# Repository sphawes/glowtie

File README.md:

## Connecting to your Glowtie

### Android

1. Turn on your Glowtie. There’s a power switch next to the micro usb jack. You should see a gold burst animation; this means the Wifi network has started.
1. On your Android phone, turn off your mobile data. This is so that your phone doesn’t try to reach the actual internet instead of the Glowtie.
1. Open your Wifi settings and look for a network named in the format “AdjectiveClothing”. For example, it could be “FancyPants” or “CoolCoat”. This is the Serial Name of your Glowtie. Connect to the network.
1. You may get a notification that the network you connected to does not have internet access, no worries! Just choose the option to stay connected if you are provided with one.
1. Now open a new tab in Google Chrome and enter the following in the address field: http://192.168.4.1
1. You should see the Glowtie control page! In your Chrome settings, choose to “Add to Home screen” to make it easier to get to in the future.

### iPhone

1. Turn on your Glowtie. You should see a gold burst animation; this means the Wifi network has started.
1. On your iPhone, navigate to Settings -> Cellular and toggle Cellular Data off. This is so that your phone doesn’t try to reach the actual internet instead of the Glowtie.
1. Open your Wifi settings and look for a network named in the format “AdjectiveClothing”. For example, it could be “FancyPants” or “CoolCoat”. This is the Serial Name of your Glowtie. Connect to the network.
1. You may get a notification that the network you connected to does not have internet access, no worries! Just choose the option to stay connected if you are provided with one.
1. Now open a new tab in Safari or Google Chrome and enter the following in the address field: http://192.168.4.1
1. You should see the Glowtie control page! In your Chrome settings, choose to “Add to Home screen” to make it easier to get to in the future. In Safari, tap the share button and select “Add to Home Screen” to do the same.

## Usage

When you load the Glowtie website, you’ll see three sliders. These represent the red, green, and blue values of the lights. When you adjust them, the title background will adjust to show you what color you’re set to.

Once you pick a color, there’s a few options for animations. Tap the button next to the animation you want, then hit the “UPDATE” button. Your Glowtie will change to whatever you selected!

The Glowtie has a built-in memory function, so once you choose a color and animation it’ll remember your choice after you turn it off. This way, you don’t need to connect to it every time you turn it on if you have it set to your favorite pattern.

## Charging

When the Glowtie has low battery, the center LED will turn red. Use a Micro USB cable to recharge your Glowtie. Make sure your Glowtie is turned off, then plug the Micro USB cable into the port next to the power switch. When you plug the other end into a USB port for power, you should see the **top** light on your Glowtie illuminate. When it’s done charging, the **bottom** light will illuminate.

## Cover

Your Glowtie optionally has a diffusion cover. The cover is held on with a friction fit. Laser cut or print `diffusion.dxf` in a white or clear material, 1/16" thick. Print `bumper.stl` in a color of your choice, and super glue the diffusion inside the bumper. The bumper can now be friction fit onto the Glowtie.

## HACK!

The Glowtie is totally open-source. All PCB design files, firmware, and physical parts are hosted on the Github page. There’s a dedicated programming header on the left side so you can add your own animations, or make it do anything you want! Just solder on a few pins and reprogram the ESP8266 over UART.

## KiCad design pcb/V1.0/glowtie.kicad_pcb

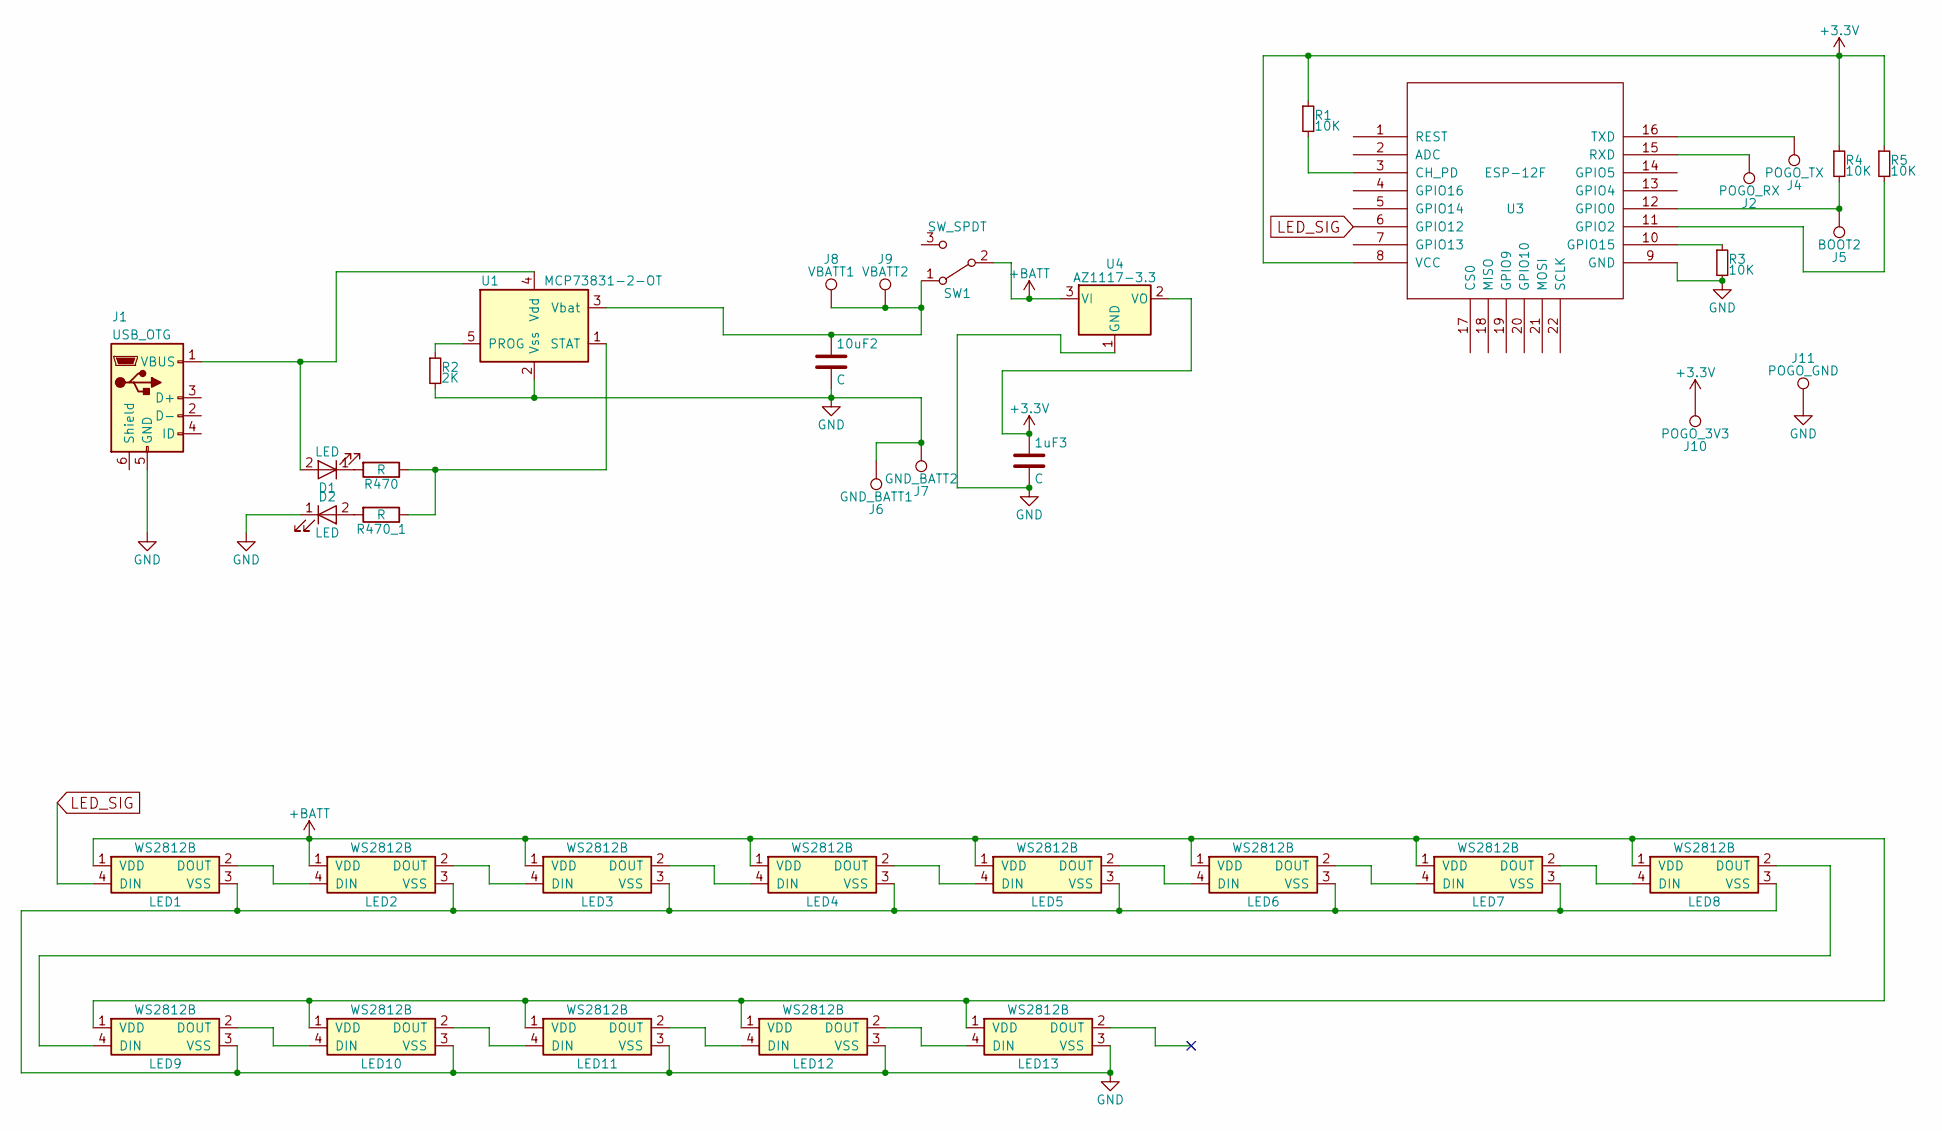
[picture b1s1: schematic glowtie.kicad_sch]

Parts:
1uF3, 10uF2: C; C_0805
D1, D2: LED; LED_0805
J1: USB_OTG; USB_Micro-B
J2: POGO_RX; TestPoint_Pad_D1.5mm
J4: POGO_TX; TestPoint_Pad_D1.5mm
J5: BOOT2; TestPoint_Pad_D1.5mm
J6: GND_BATT1; Measurement_Point_Square-SMD-Pad_Big
J7: GND_BATT2; Measurement_Point_Square-SMD-Pad_Big
J8: VBATT1; Measurement_Point_Round-SMD-Pad_Big
J9: VBATT2; Measurement_Point_Round-SMD-Pad_Big
J10: POGO_3V3; TestPoint_Pad_D1.5mm
J11: POGO_GND; TestPoint_Pad_D1.5mm
LED1, LED2, LED3, LED4, LED5, LED6, LED7, LED8, LED9, LED10, LED11, LED12, LED13: WS2812B; LED_WS2812B-PLCC4
R1, R3, R4, R5: 10K; R_0805
R2: 2K; R_0805
R470, R470_1: R; R_0805
SW1: SW_SPDT; SW_SPDT_PCM12
U1: MCP73831-2-OT; SOT-23-5
U3: ESP-12F; ESP-12E_SMD
U4: AZ1117-3.3; SOT-223-3_TabPin2

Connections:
+3V3: 1uF3.1, J10.1, R1.1, R4.1, R5.1, U3.8 (VCC), U4.2 (VO)
+BATT: LED1.1 (VDD), LED2.1 (VDD), LED3.1 (VDD), LED4.1 (VDD), LED5.1 (VDD), LED6.1 (VDD), LED7.1 (VDD), LED8.1 (VDD), LED9.1 (VDD), LED10.1 (VDD), LED11.1 (VDD), LED12.1 (VDD), LED13.1 (VDD), SW1.2 (B), U4.3 (VI)
GND: 1uF3.2, 10uF2.2, D2.1 (K), J1.5 (GND), J6.1, J7.1, J11.1, LED1.3 (VSS), LED2.3 (VSS), LED3.3 (VSS), LED4.3 (VSS), LED5.3 (VSS), LED6.3 (VSS), LED7.3 (VSS), LED8.3 (VSS), LED9.3 (VSS), LED10.3 (VSS), LED11.3 (VSS), LED12.3 (VSS), LED13.3 (VSS), R2.2, R3.2, U1.2 (Vss), U3.9 (GND), U4.1 (GND)
LED_SIG: LED1.4 (DIN), U3.6 (GPIO12)
unnamed: D1.2 (A), J1.1 (VBUS), U1.4 (Vdd)
unnamed: D1.1 (K), R470.2
unnamed: D2.2 (A), R470_1.2
unnamed: LED1.2 (DOUT), LED2.4 (DIN)
unnamed: LED2.2 (DOUT), LED3.4 (DIN)
unnamed: LED3.2 (DOUT), LED4.4 (DIN)
unnamed: LED4.2 (DOUT), LED5.4 (DIN)
unnamed: LED5.2 (DOUT), LED6.4 (DIN)
unnamed: LED6.2 (DOUT), LED7.4 (DIN)
unnamed: LED7.2 (DOUT), LED8.4 (DIN)
unnamed: LED8.2 (DOUT), LED9.4 (DIN)
unnamed: LED9.2 (DOUT), LED10.4 (DIN)
unnamed: LED10.2 (DOUT), LED11.4 (DIN)
unnamed: LED11.2 (DOUT), LED12.4 (DIN)
unnamed: LED12.2 (DOUT), LED13.4 (DIN)
unnamed: 10uF2.1, J8.1, J9.1, SW1.1 (A), U1.3 (Vbat)
unnamed: R2.1, U1.5 (PROG)
unnamed: R470.1, R470_1.1, U1.1 (STAT)
unnamed: R1.2, U3.3 (CH_PD)
unnamed: J5.1, R4.2, U3.12 (GPIO0)
unnamed: R5.2, U3.11 (GPIO2)
unnamed: R3.1, U3.10 (GPIO15)
unnamed: J2.1, U3.15 (RXD)
unnamed: J4.1, U3.16 (TXD)

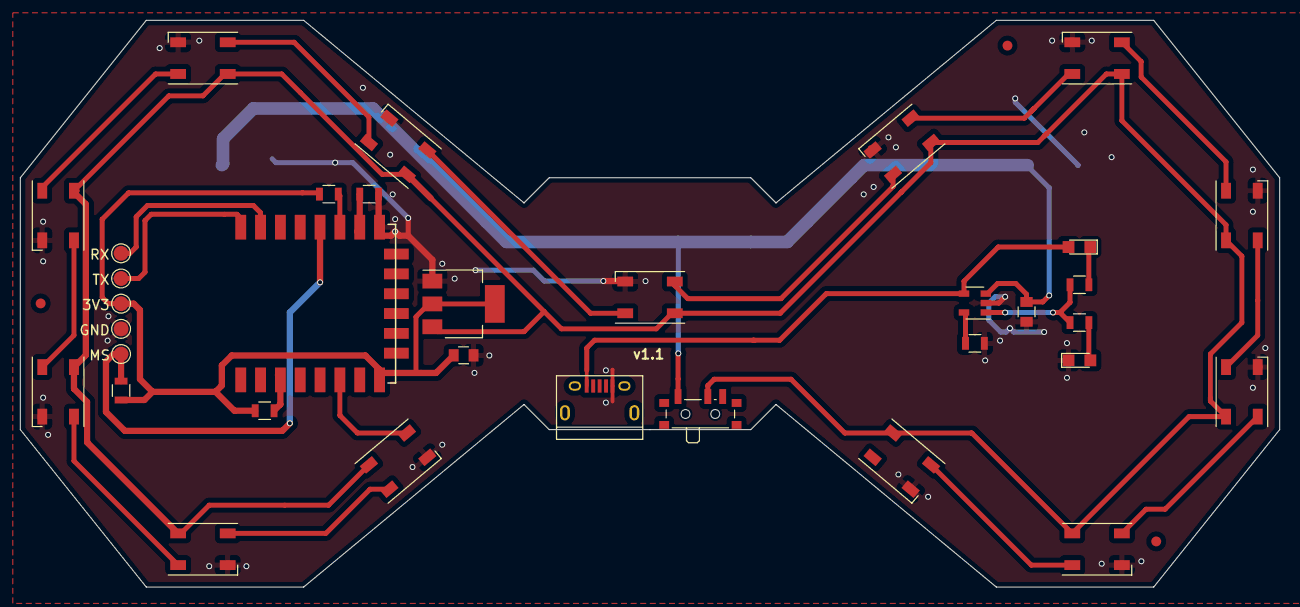
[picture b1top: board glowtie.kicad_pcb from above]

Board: 2 copper layers, 127.0 x 57.1 mm, 38 parts (0 on the bottom side), 28 nets.

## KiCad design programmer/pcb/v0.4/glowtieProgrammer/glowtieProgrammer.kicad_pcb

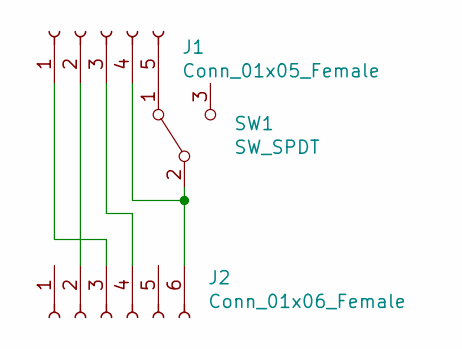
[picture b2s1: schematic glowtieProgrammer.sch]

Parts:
J1: Conn_01x05_Female; Pin_Header_Straight_1x05_Pitch2.54mm
J2: Conn_01x06_Female; Pin_Header_Straight_1x06_Pitch2.54mm
SW1: SW_SPDT; SW_SPDT_PCM12

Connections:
unnamed: J1.1, J2.3
unnamed: J1.2, J2.2
unnamed: J1.3, J2.4
unnamed: J1.4, J2.6, SW1.2 (B)
unnamed: J1.5, SW1.1 (A)

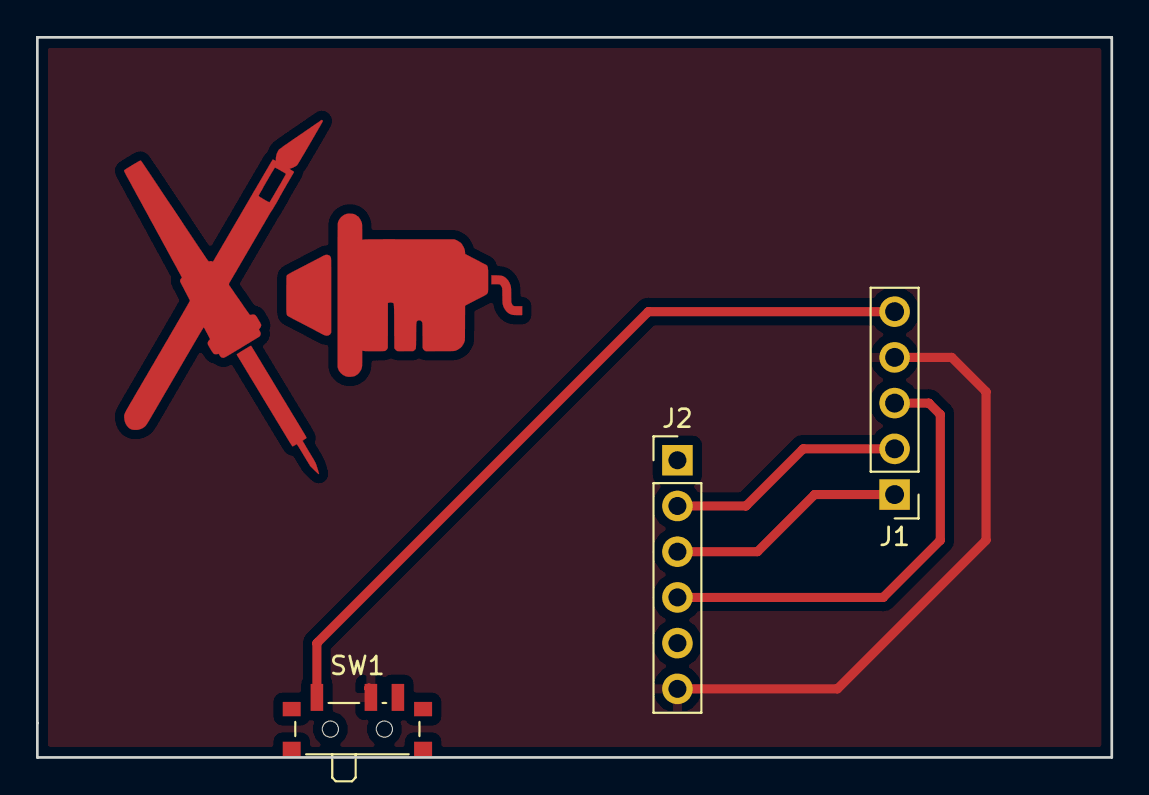
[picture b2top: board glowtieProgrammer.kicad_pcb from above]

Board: 2 copper layers, 59.7 x 40.0 mm, 3 parts (0 on the bottom side), 5 nets.

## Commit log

2019-02-02 adding directory for v0.4 firmware and boot test firmware
2019-02-02 made boot burst gold, firmware flash default mode 0, and added eeprom for color and mode selection between boots
2019-02-03 readme formatting
2019-02-03 adding line art image
2019-02-03 added image to readme
2019-02-17 added programmer cad, updated glowtie cad, cleaned up directory structure
2019-02-17 added images, updated readme
2019-05-19 second to last firmware push
2019-07-28 updated firmware and cad for v1.0
2020-02-11 Set theme jekyll-theme-slate
2023-07-29 updating pcb to v1.1 with better grounding, more widely used LDO pinout
2023-12-10 adds v1.1 and docs page
2023-12-10 updates readme
2023-12-10 updates readme and adds image
2023-12-12 Create CNAME
2023-12-18 Update CNAME
2026-01-11 pushing up from melange
